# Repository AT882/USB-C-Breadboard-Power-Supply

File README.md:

# USB-C Breadboard Power Supply

A compact USB-C Power Delivery (PD) breadboard power supply designed for electronics prototyping and development.
The board is based on the **CH224K USB-PD sink/trigger IC** and is designed to obtain power from compatible USB-C PD adapters and provide it conveniently to standard breadboard power rails.

<h2>PCB 3D View</h2>

<h3>Front View</h3>

<h3>Back View</h3>

## Features

- USB Type-C power input
- CH224K USB-PD sink/trigger controller
- Selectable USB-PD voltage configuration
- 3-position DIP switch
- Breadboard-compatible 2.54 mm headers
- Power indicator LED
- 100 µF input/output filtering capacitors
- Compact PCB design
- Custom AT PCB logo
- KiCad schematic and PCB source files included

---

## Hardware

### Main Components

| Component | Description |
|---|---|
| CH224K | USB Power Delivery sink/trigger controller |
| USB-C Receptacle | USB-C power input |
| DIP Switch | PD voltage configuration |
| LED | Power indication |
| 100 µF / 35 V | Power filtering capacitors |
| 2.54 mm Headers | Breadboard power connections |

---

## USB-C Power Delivery

The CH224K communicates with a compatible USB-C PD power adapter and requests an appropriate power profile according to the hardware configuration.

> **Important:** Available output voltages and current depend on the USB-C PD adapter being used and the CH224K configuration.

A charger rated for 33 W does not continuously deliver 33 W to the board. The connected load draws the current it requires, up to the limits of the negotiated USB-PD profile and the hardware.

---

## Breadboard Interface

The PCB is designed to plug directly into the positive and negative power rails of a standard solderless breadboard using **2.54 mm male headers**.

This makes it useful for quickly powering:

- Microcontroller projects
- Sensors
- Development boards
- Analog circuits
- Digital circuits
- General breadboard prototypes

---

## Project Structure

```text
USB-C-Breadboard-Power-Supply/
│
├── USB-C Breadboard Power Supply/
│   ├── USB-C Breadboard Power Supply.kicad_pro
│   ├── USB-C Breadboard Power Supply.kicad_sch
│   ├── USB-C Breadboard Power Supply.kicad_pcb
│   │
│   ├── My_Logos.pretty/
│   │   └── AT_Logo.kicad_mod
│   │
│   └── Other KiCad project files
│
├── PCB_3D_F.png
├── PCB_3D_B.png
└── README.md

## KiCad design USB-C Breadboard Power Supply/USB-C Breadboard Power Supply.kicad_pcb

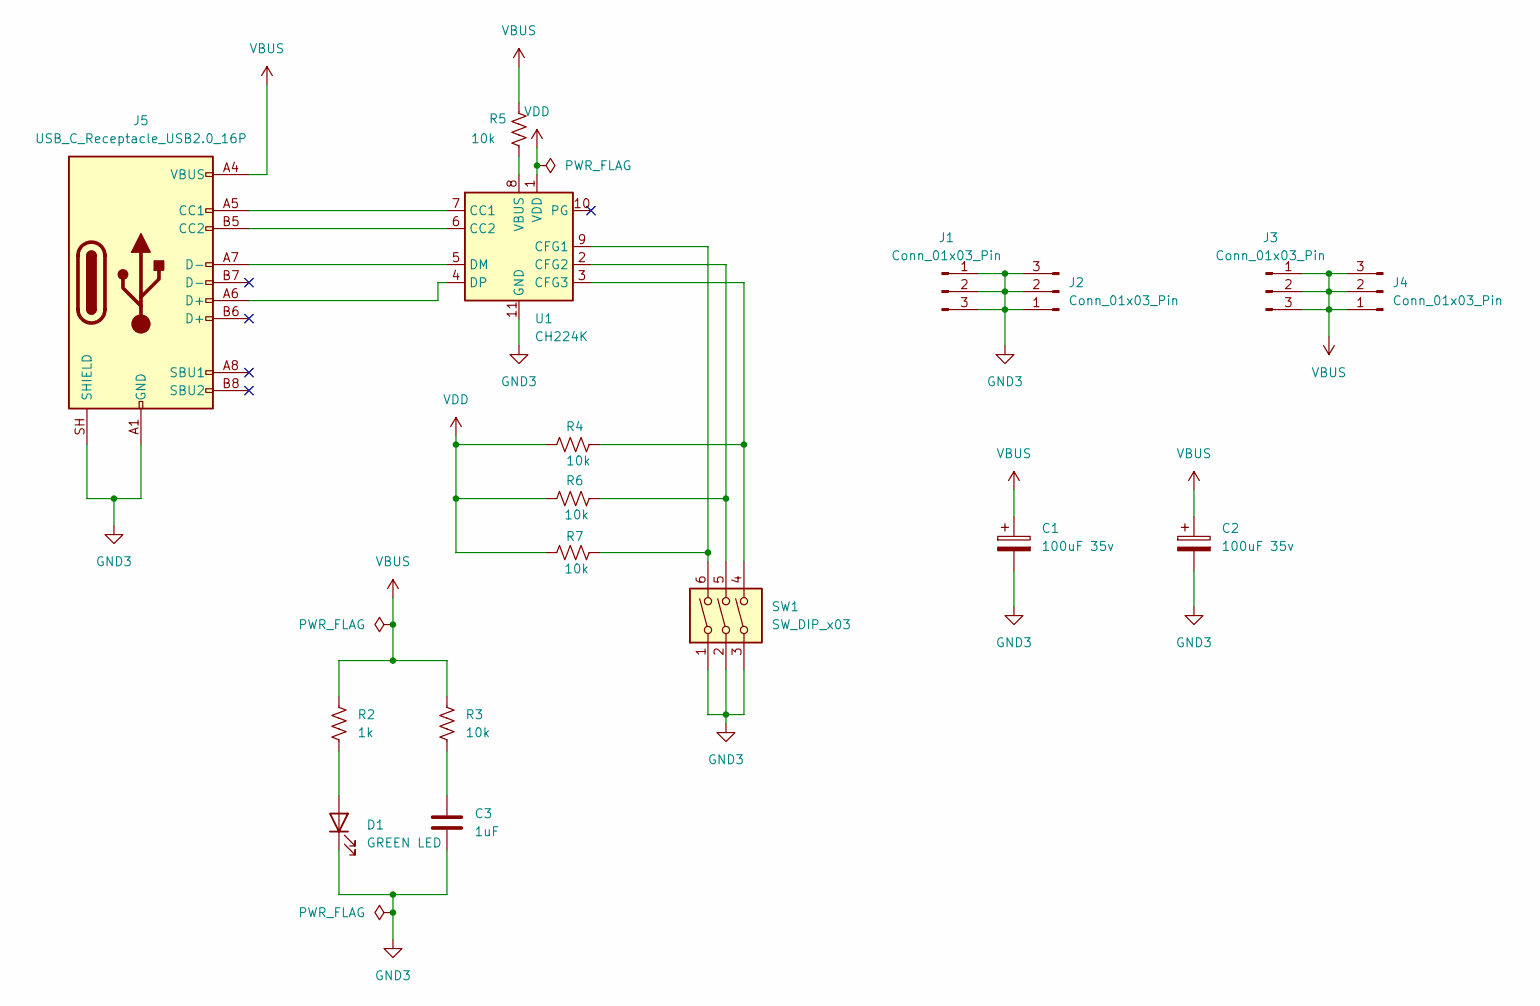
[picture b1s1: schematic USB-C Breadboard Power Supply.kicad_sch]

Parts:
C1, C2: 100uF 35v; CP_Elec_8x10.5
C3: 1uF; C_1206_3216Metric_Pad1.33x1.80mm_HandSolder
D1: GREEN LED; LED_1206_3216Metric_Pad1.42x1.75mm_HandSolder
J1, J2, J3, J4: Conn_01x03_Pin; PinHeader_1x03_P2.54mm_Vertical
J5: USB_C_Receptacle_USB2.0_16P; USB_C_Receptacle_XKB_U262-16XN-4BVC11
R2: 1k; R_1206_3216Metric_Pad1.30x1.75mm_HandSolder
R3, R4, R5, R6, R7: 10k; R_1206_3216Metric_Pad1.30x1.75mm_HandSolder
SW1: SW_DIP_x03; SW_DIP_SPSTx03_Slide_9.78x9.8mm_W7.62mm_P2.54mm
U1: CH224K; SSOP-10-1EP_3.9x4.9mm_P1mm_EP2.1x3.3mm

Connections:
GND3: C1.2, C2.2, C3.2, D1.1 (K), J1.1, J1.2, J1.3, J2.1, J2.2, J2.3, J5.A1 (GND), J5.A12 (GND), J5.B1 (GND), J5.B12 (GND), J5.SH (SHIELD), SW1.1, SW1.2, SW1.3, U1.11 (GND)
unnamed: C3.1, R3.2
unnamed: D1.2 (A), R2.2
unnamed: J5.A5 (CC1), U1.7 (CC1)
unnamed: J5.B5 (CC2), U1.6 (CC2)
unnamed: R7.2, SW1.6, U1.9 (CFG1)
unnamed: R6.2, SW1.5, U1.2 (CFG2)
unnamed: R4.2, SW1.4, U1.3 (CFG3)
unnamed: J5.A7 (D-), U1.5 (DM)
unnamed: J5.A6 (D+), U1.4 (DP)
unnamed: R5.2, U1.8 (VBUS)
VBUS: C1.1, C2.1, J3.1, J3.2, J3.3, J4.1, J4.2, J4.3, J5.A4 (VBUS), J5.A9 (VBUS), J5.B4 (VBUS), J5.B9 (VBUS), R2.1, R3.1, R5.1
VDD: R4.1, R6.1, R7.1, U1.1 (VDD)

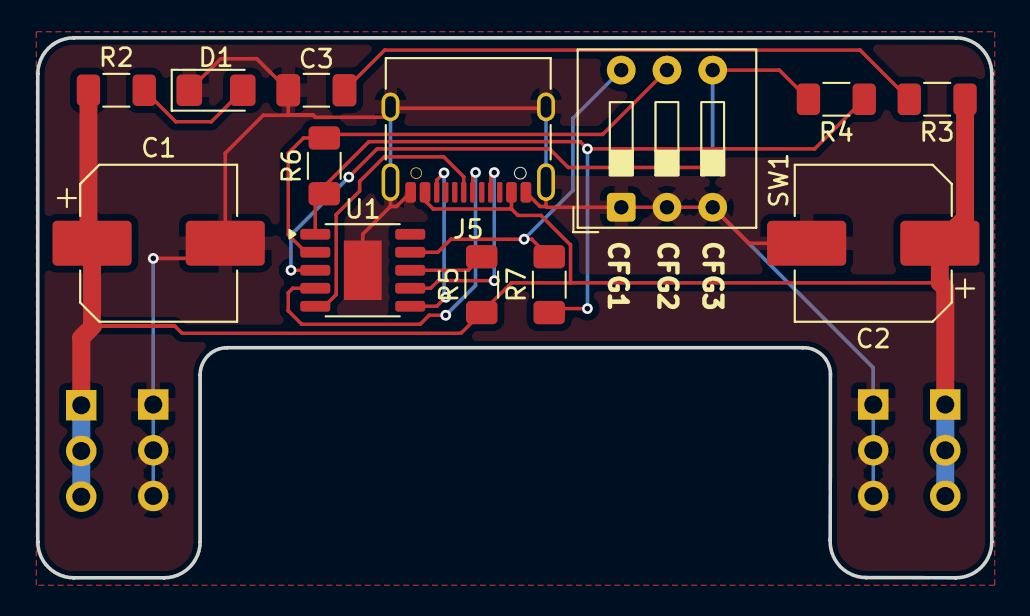
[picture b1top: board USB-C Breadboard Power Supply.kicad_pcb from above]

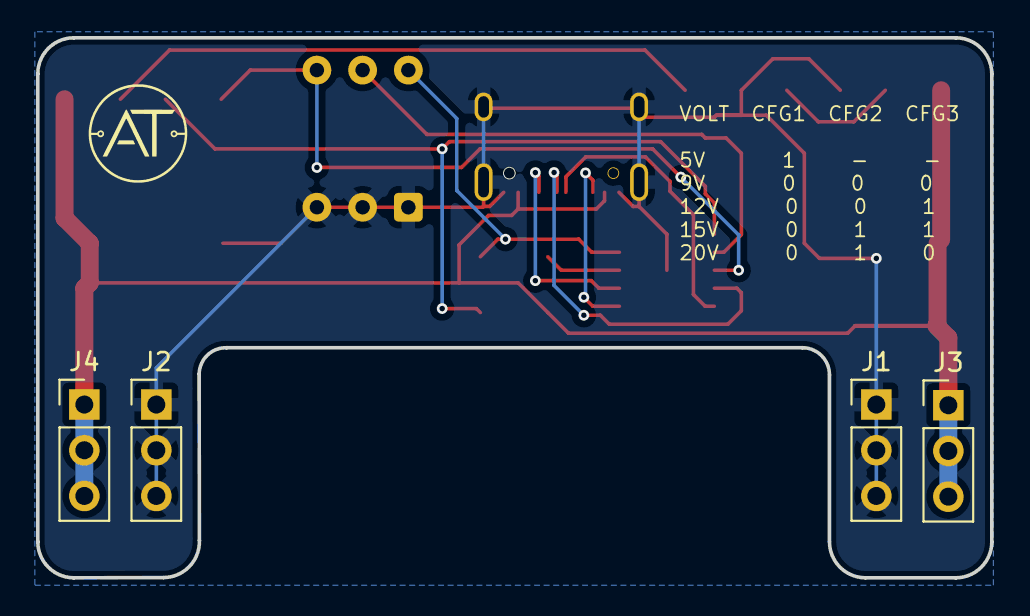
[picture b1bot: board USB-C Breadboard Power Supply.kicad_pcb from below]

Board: 2 copper layers, 53.0 x 30.0 mm, 18 parts (5 on the bottom side), 13 nets.

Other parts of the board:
.: LOGO; AT_Logo
